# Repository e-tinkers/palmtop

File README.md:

# PalmTop - STM32G070-based Handheld

This repository contains the Kicad schematic and PCB files, plus hardware test sketch for 
[PalmTop](https://www.e-tinkers.com/2023/06/build-a-palmtop-handheld-with-stm32g070-part-1/) project.

![PalmTop - STM32G070-based 
handheld](https://www.e-tinkers.com/wp-content/uploads/2023/06/PalmTop_STM32G070.png)

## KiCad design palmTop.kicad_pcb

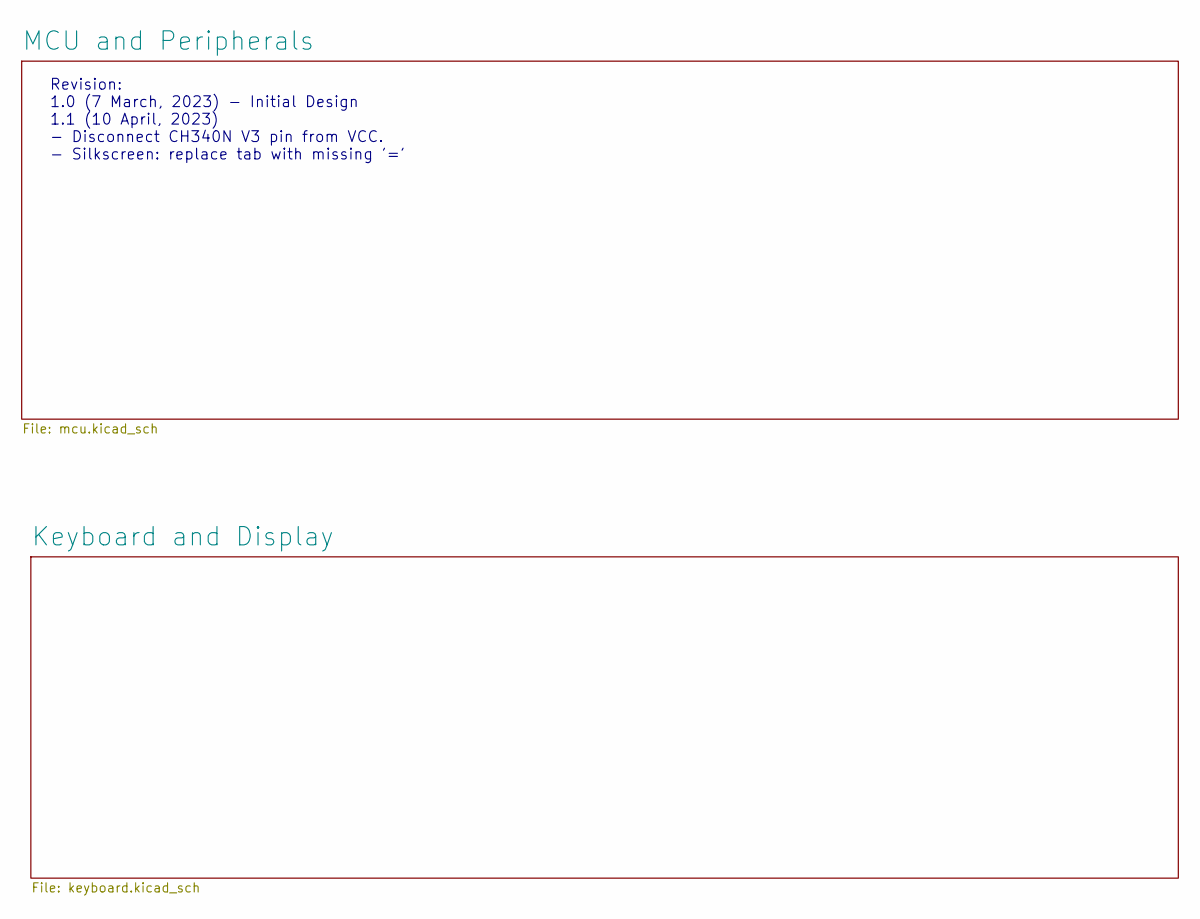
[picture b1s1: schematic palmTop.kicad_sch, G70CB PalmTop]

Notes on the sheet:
Revision: 1.0 (7 March, 2023) - Initial Design 1.1 (10 April, 2023) - Disconnect CH340N V3 pin from VCC. - Silkscreen: replace tab with missing '='

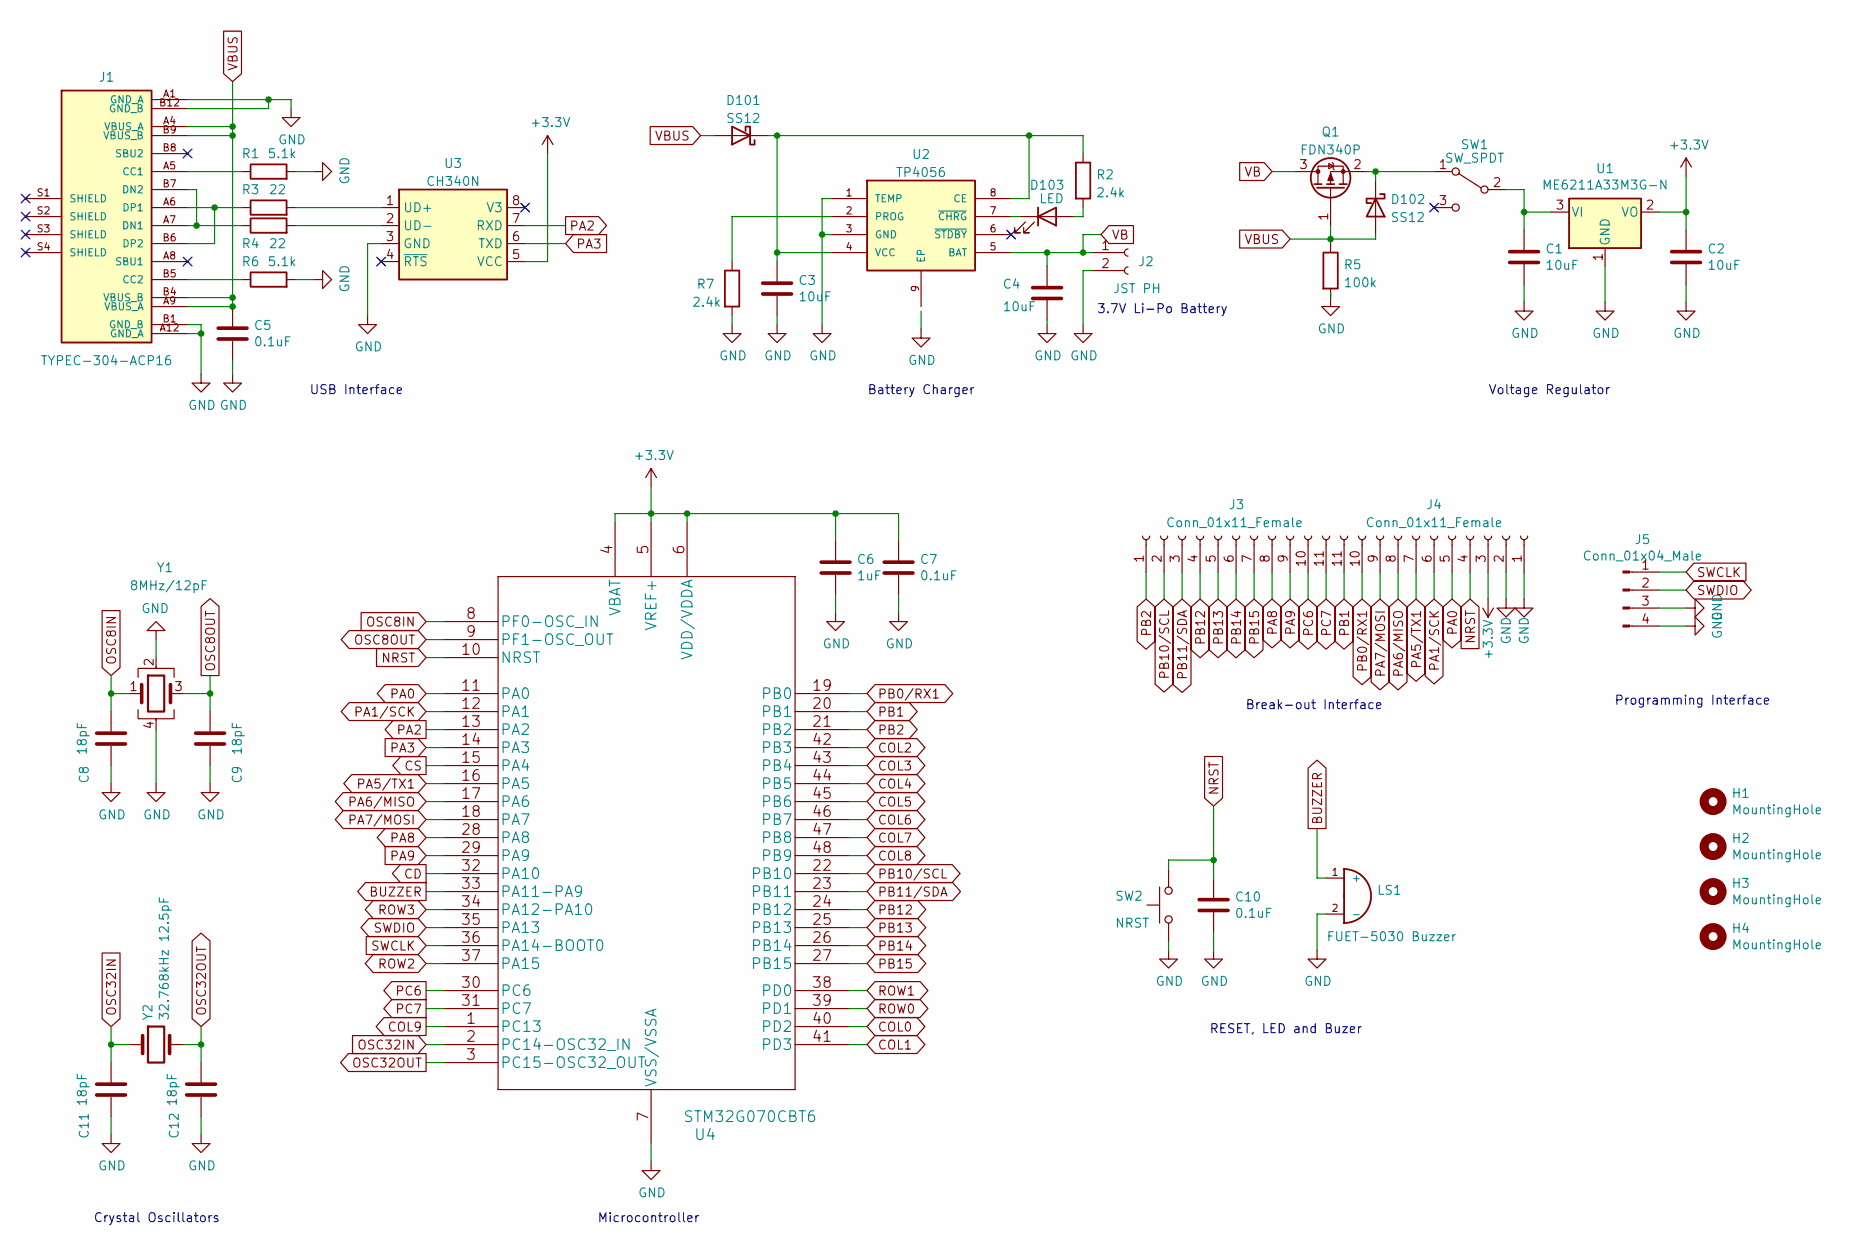
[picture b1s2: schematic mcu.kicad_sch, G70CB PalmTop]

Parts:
C1, C2, C3, C4: 10uF; C_0603_1608Metric_Pad1.08x0.95mm_HandSolder
C5, C7, C10: 0.1uF; C_0603_1608Metric_Pad1.08x0.95mm_HandSolder
C6: 1uF; C_0603_1608Metric_Pad1.08x0.95mm_HandSolder
C8, C9, C11, C12: 18pF; C_0603_1608Metric_Pad1.08x0.95mm_HandSolder
D101, D102: SS12; D_SMA
D103: LED; LED_0603_1608Metric_Pad1.05x0.95mm_HandSolder
H1, H2, H3, H4: MountingHole; MountingHole_3.2mm_M3
J1: TYPEC-304-ACP16; XUNPU_TYPEC-304-ACP16
J2: JST PH; JST_PH_S2B-PH-K_1x02_P2.00mm_Horizontal
J3, J4: Conn_01x11_Female; PinSocket_1x11_P2.54mm_Horizontal
J5: Conn_01x04_Male; PinHeader_1x04_P2.54mm_Horizontal
LS1: FUET-5030 Buzzer; FUET-5030-BUZZER
Q1: FDN340P; SOT-23
R1, R6: 5.1k; R_0603_1608Metric_Pad0.98x0.95mm_HandSolder
R2, R7: 2.4k; R_0603_1608Metric_Pad0.98x0.95mm_HandSolder
R3, R4: 22; R_0603_1608Metric_Pad0.98x0.95mm_HandSolder
R5: 100k; R_0603_1608Metric_Pad0.98x0.95mm_HandSolder
SW1: SW_SPDT; SW_SPDT_XKB_SK-3390A-L1
SW2: NRST; SW_TS-1185-X-X
U1: ME6211A33M3G-N; SOT-23
U2: TP4056; SOP127P600X175-9N
U3: CH340N; SOP-8_3.76x4.96mm_P1.27mm
U4: STM32G070CBT6; LQFP-48_7x7mm_P0.5mm
Y1: 8MHz/12pF; Crystal_SMD_3225-4Pin_3.2x2.5mm
Y2: 32.768kHz 12.5pF; Crystal_SMD_3215-2Pin_3.2x1.5mm

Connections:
BUZZER: LS1.1 (+), U4.33 (PA11-PA9)
+3V3: C2.1, C6.1, C7.1, J4.3, U1.2 (VO), U3.5 (VCC), U4.4 (VBAT), U4.5 (VREF+), U4.6 (VDD/VDDA); also elsewhere on the board
CD: U4.32 (PA10); also elsewhere on the board
COL0: U4.40 (PD2); also elsewhere on the board
COL1: U4.41 (PD3); also elsewhere on the board
COL2: U4.42 (PB3); also elsewhere on the board
COL3: U4.43 (PB4); also elsewhere on the board
COL4: U4.44 (PB5); also elsewhere on the board
COL5: U4.45 (PB6); also elsewhere on the board
COL6: U4.46 (PB7); also elsewhere on the board
COL7: U4.47 (PB8); also elsewhere on the board
COL8: U4.48 (PB9); also elsewhere on the board
COL9: U4.1 (PC13); also elsewhere on the board
CS: U4.15 (PA4); also elsewhere on the board
GND: C1.2, C2.2, C3.2, C4.2, C5.2, C6.2, C7.2, C8.2, C9.2, C10.1, C11.2, C12.2, J1.A1 (GND_A), J1.A12 (GND_A), J1.B1 (GND_B), J1.B12 (GND_B), J2.2, J4.1, J4.2, J5.3, J5.4, LS1.2 (-), R1.2, R5.2, R6.2, R7.2, SW2.1, U1.1 (GND), U2.1 (TEMP), U2.3 (GND), U3.3 (GND), U4.7 (VSS/VSSA), Y1.2, Y1.4; also elsewhere on the board
NRST: C10.2, J4.4, SW2.2, U4.10 (NRST); also elsewhere on the board
unnamed: C1.1, SW1.2 (B), U1.3 (VI)
unnamed: C3.1, D101.1 (K), R2.1, U2.4 (VCC), U2.8 (CE)
unnamed: D102.1 (K), Q1.2 (S), SW1.1 (A)
unnamed: D103.1 (K), U2.7 (~CHRG)
unnamed: D103.2 (A), R2.2
unnamed: J1.A5 (CC1), R1.1
unnamed: J1.A6 (DP1), J1.B6 (DP2), R3.1
unnamed: J1.A7 (DN1), J1.B7 (DN2), R4.1
unnamed: J1.B5 (CC2), R6.1
unnamed: R3.2, U3.1 (UD+)
unnamed: R4.2, U3.2 (UD-)
unnamed: R7.1, U2.2 (PROG)
OSC8IN: C8.1, U4.8 (PF0-OSC_IN), Y1.1
OSC8OUT: C9.1, U4.9 (PF1-OSC_OUT), Y1.3
OSC32IN: C11.1, U4.2 (PC14-OSC32_IN), Y2.1
OSC32OUT: C12.1, U4.3 (PC15-OSC32_OUT), Y2.2
PA0: J4.5, U4.11 (PA0)
PA1/SCK: J4.6, U4.12 (PA1); also elsewhere on the board
PA2: U3.7 (RXD), U4.13 (PA2)
PA3: U3.6 (TXD), U4.14 (PA3)
PA5/TX1: J4.7, U4.16 (PA5)
PA6/MISO: J4.8, U4.17 (PA6)
PA7/MOSI: J4.9, U4.18 (PA7); also elsewhere on the board
PA8: J3.8, U4.28 (PA8)
PA9: J3.9, U4.29 (PA9)
PB0/RX1: J4.10, U4.19 (PB0)
PB1: J4.11, U4.20 (PB1)
PB2: J3.1, U4.21 (PB2)
PB10/SCL: J3.2, U4.22 (PB10)
PB11/SDA: J3.3, U4.23 (PB11)
PB12: J3.4, U4.24 (PB12)
PB13: J3.5, U4.25 (PB13)
PB14: J3.6, U4.26 (PB14)
PB15: J3.7, U4.27 (PB15)
PC6: J3.10, U4.30 (PC6)
PC7: J3.11, U4.31 (PC7)
ROW0: U4.39 (PD1); also elsewhere on the board
ROW1: U4.38 (PD0); also elsewhere on the board
ROW2: U4.37 (PA15); also elsewhere on the board
ROW3: U4.34 (PA12-PA10); also elsewhere on the board
SWCLK: J5.1, U4.36 (PA14-BOOT0)
SWDIO: J5.2, U4.35 (PA13)
VB: C4.1, J2.1, Q1.3 (D), U2.5 (BAT)
VBUS: C5.1, D101.2 (A), D102.2 (A), J1.A4 (VBUS_A), J1.A9 (VBUS_A), J1.B4 (VBUS_B), J1.B9 (VBUS_B), Q1.1 (G), R5.1

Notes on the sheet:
RESET, LED and Buzer
Battery Charger
Microcontroller
USB Interface
Voltage Regulator
3.7V Li-Po Battery
Crystal Oscillators
Programming Interface
Break-out Interface

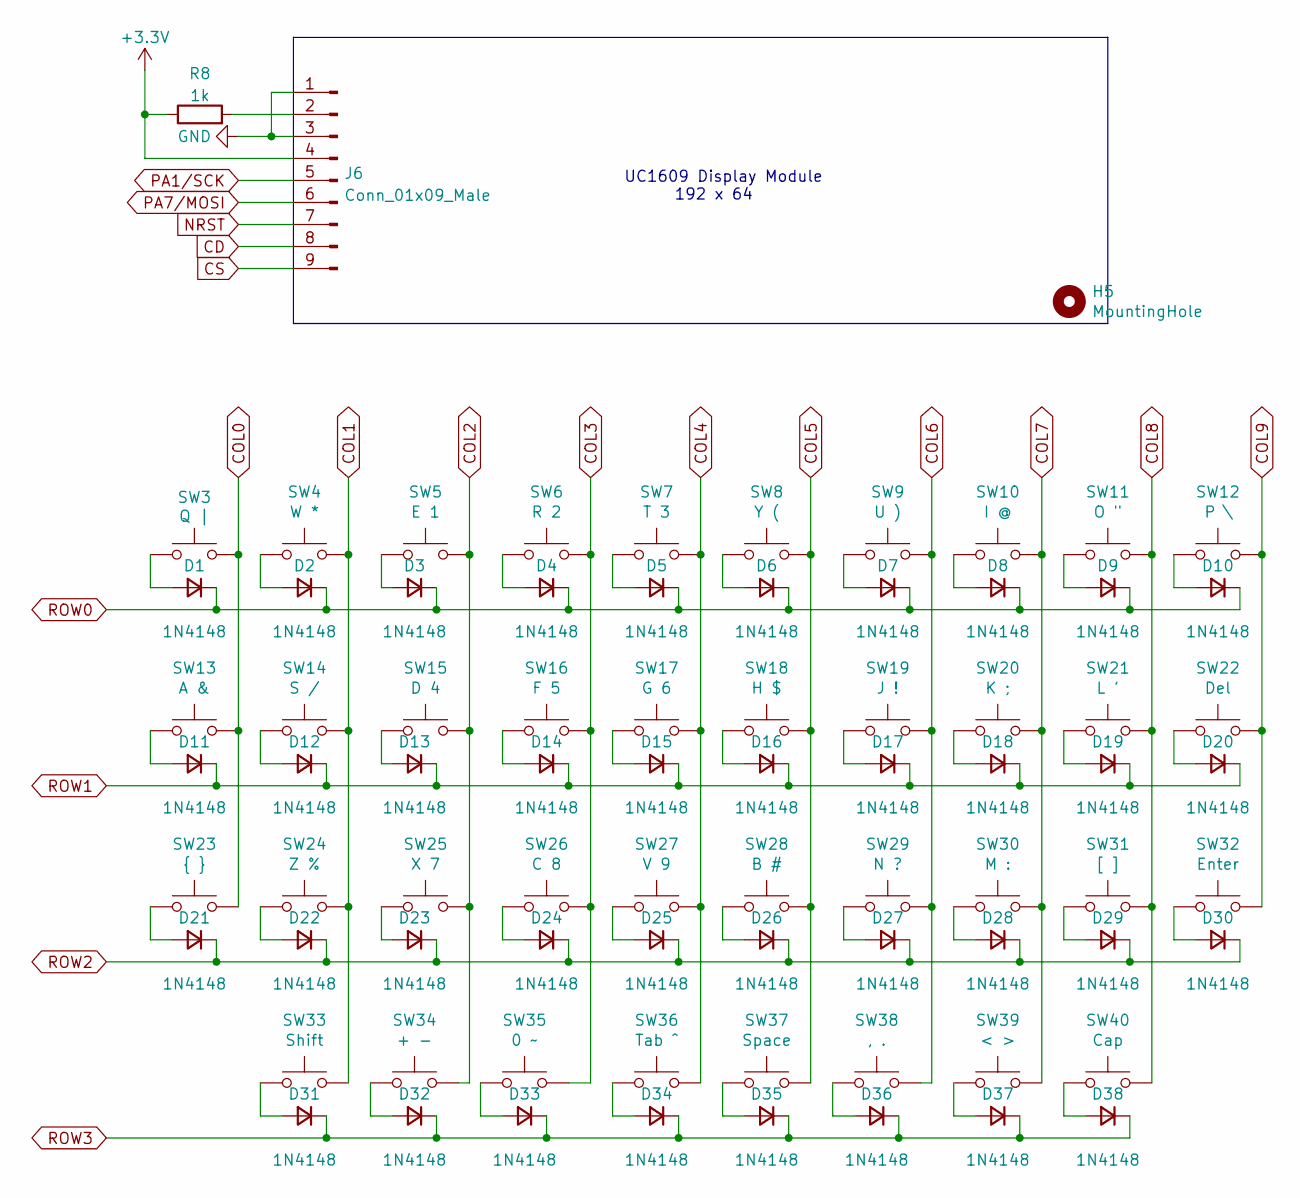
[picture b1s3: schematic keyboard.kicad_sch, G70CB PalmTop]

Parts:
D1, D2, D3, D4, D5, D6, D7, D8, D9, D10, D11, D12, D13, D14, D15, D16, D17, D18, D19, D20, D21, D22, D23, D24, D25, D26, D27, D28, D29, D30, D31, D32, D33, D34, D35, D36, D37, D38: 1N4148; D_SOD-123
H5: MountingHole; MountingHole_2.7mm_M2.5
J6: Conn_01x09_Male; PinHeader_1x09_P2.54mm_Vertical
R8: 1k; R_0603_1608Metric_Pad0.98x0.95mm_HandSolder
SW3: Q |; SW_PUSH_6mm_XKB_TC-1102-X-X-X
SW4: W *; SW_PUSH_6mm_XKB_TC-1102-X-X-X
SW5: E 1; SW_PUSH_6mm_XKB_TC-1102-X-X-X
SW6: R 2; SW_PUSH_6mm_XKB_TC-1102-X-X-X
SW7: T 3; SW_PUSH_6mm_XKB_TC-1102-X-X-X
SW8: Y (; SW_PUSH_6mm_XKB_TC-1102-X-X-X
SW9: U ); SW_PUSH_6mm_XKB_TC-1102-X-X-X
SW10: I @; SW_PUSH_6mm_XKB_TC-1102-X-X-X
SW11: O "; SW_PUSH_6mm_XKB_TC-1102-X-X-X
SW12: P \; SW_PUSH_6mm_XKB_TC-1102-X-X-X
SW13: A &; SW_PUSH_6mm_XKB_TC-1102-X-X-X
SW14: S /; SW_PUSH_6mm_XKB_TC-1102-X-X-X
SW15: D 4; SW_PUSH_6mm_XKB_TC-1102-X-X-X
SW16: F 5; SW_PUSH_6mm_XKB_TC-1102-X-X-X
SW17: G 6; SW_PUSH_6mm_XKB_TC-1102-X-X-X
SW18: H $; SW_PUSH_6mm_XKB_TC-1102-X-X-X
SW19: J !; SW_PUSH_6mm_XKB_TC-1102-X-X-X
SW20: K ;; SW_PUSH_6mm_XKB_TC-1102-X-X-X
SW21: L '; SW_PUSH_6mm_XKB_TC-1102-X-X-X
SW22: Del; SW_PUSH_6mm_XKB_TC-1102-X-X-X
SW23: { }; SW_PUSH_6mm_XKB_TC-1102-X-X-X
SW24: Z %; SW_PUSH_6mm_XKB_TC-1102-X-X-X
SW25: X 7; SW_PUSH_6mm_XKB_TC-1102-X-X-X
SW26: C 8; SW_PUSH_6mm_XKB_TC-1102-X-X-X
SW27: V 9; SW_PUSH_6mm_XKB_TC-1102-X-X-X
SW28: B #; SW_PUSH_6mm_XKB_TC-1102-X-X-X
SW29: N ?; SW_PUSH_6mm_XKB_TC-1102-X-X-X
SW30: M :; SW_PUSH_6mm_XKB_TC-1102-X-X-X
SW31: [ ]; SW_PUSH_6mm_XKB_TC-1102-X-X-X
SW32: Enter; SW_PUSH_6mm_XKB_TC-1102-X-X-X
SW33: Shift; SW_PUSH_6mm_XKB_TC-1102-X-X-X
SW34: + -; SW_PUSH_6mm_XKB_TC-1102-X-X-X
SW35: 0 ~; SW_PUSH_6mm_XKB_TC-1102-X-X-X
SW36: Tab ^; SW_PUSH_6mm_XKB_TC-1102-X-X-X
SW37: Space; SW_PUSH_6mm_XKB_TC-1102-X-X-X
SW38: , .; SW_PUSH_6mm_XKB_TC-1102-X-X-X
SW39: < >; SW_PUSH_6mm_XKB_TC-1102-X-X-X
SW40: Cap; SW_PUSH_6mm_XKB_TC-1102-X-X-X

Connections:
+3V3: J6.4, R8.1; also elsewhere on the board
CD: J6.8; also elsewhere on the board
COL0: SW3.2, SW13.2, SW23.2; also elsewhere on the board
COL1: SW4.2, SW14.2, SW24.2, SW33.2; also elsewhere on the board
COL2: SW5.2, SW15.2, SW25.2, SW34.2; also elsewhere on the board
COL3: SW6.2, SW16.2, SW26.2, SW35.2; also elsewhere on the board
COL4: SW7.2, SW17.2, SW27.2, SW36.2; also elsewhere on the board
COL5: SW8.2, SW18.2, SW28.2, SW37.2; also elsewhere on the board
COL6: SW9.2, SW19.2, SW29.2, SW38.2; also elsewhere on the board
COL7: SW10.2, SW20.2, SW30.2, SW39.2; also elsewhere on the board
COL8: SW11.2, SW21.2, SW31.2, SW40.2; also elsewhere on the board
COL9: SW12.2, SW22.2, SW32.2; also elsewhere on the board
CS: J6.9; also elsewhere on the board
GND: J6.1, J6.3; also elsewhere on the board
NRST: J6.7; also elsewhere on the board
unnamed: D1.2 (A), SW3.1
unnamed: D2.2 (A), SW4.1
unnamed: D3.2 (A), SW5.1
unnamed: D4.2 (A), SW6.1
unnamed: D5.2 (A), SW7.1
unnamed: D6.2 (A), SW8.1
unnamed: D7.2 (A), SW9.1
unnamed: D8.2 (A), SW10.1
unnamed: D9.2 (A), SW11.1
unnamed: D10.2 (A), SW12.1
unnamed: D11.2 (A), SW13.1
unnamed: D12.2 (A), SW14.1
unnamed: D13.2 (A), SW15.1
unnamed: D14.2 (A), SW16.1
unnamed: D15.2 (A), SW17.1
unnamed: D16.2 (A), SW18.1
unnamed: D17.2 (A), SW19.1
unnamed: D18.2 (A), SW20.1
unnamed: D19.2 (A), SW21.1
unnamed: D20.2 (A), SW22.1
unnamed: D21.2 (A), SW23.1
unnamed: D22.2 (A), SW24.1
unnamed: D23.2 (A), SW25.1
unnamed: D24.2 (A), SW26.1
unnamed: D25.2 (A), SW27.1
unnamed: D26.2 (A), SW28.1
unnamed: D27.2 (A), SW29.1
unnamed: D28.2 (A), SW30.1
unnamed: D29.2 (A), SW31.1
unnamed: D30.2 (A), SW32.1
unnamed: D31.2 (A), SW33.1
unnamed: D32.2 (A), SW34.1
unnamed: D33.2 (A), SW35.1
unnamed: D34.2 (A), SW36.1
unnamed: D35.2 (A), SW37.1
unnamed: D36.2 (A), SW38.1
unnamed: D37.2 (A), SW39.1
unnamed: D38.2 (A), SW40.1
unnamed: J6.2, R8.2
PA1/SCK: J6.5; also elsewhere on the board
PA7/MOSI: J6.6; also elsewhere on the board
ROW0: D1.1 (K), D2.1 (K), D3.1 (K), D4.1 (K), D5.1 (K), D6.1 (K), D7.1 (K), D8.1 (K), D9.1 (K), D10.1 (K); also elsewhere on the board
ROW1: D11.1 (K), D12.1 (K), D13.1 (K), D14.1 (K), D15.1 (K), D16.1 (K), D17.1 (K), D18.1 (K), D19.1 (K), D20.1 (K); also elsewhere on the board
ROW2: D21.1 (K), D22.1 (K), D23.1 (K), D24.1 (K), D25.1 (K), D26.1 (K), D27.1 (K), D28.1 (K), D29.1 (K), D30.1 (K); also elsewhere on the board
ROW3: D31.1 (K), D32.1 (K), D33.1 (K), D34.1 (K), D35.1 (K), D36.1 (K), D37.1 (K), D38.1 (K); also elsewhere on the board

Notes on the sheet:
UC1609 Display Module 192 x 64

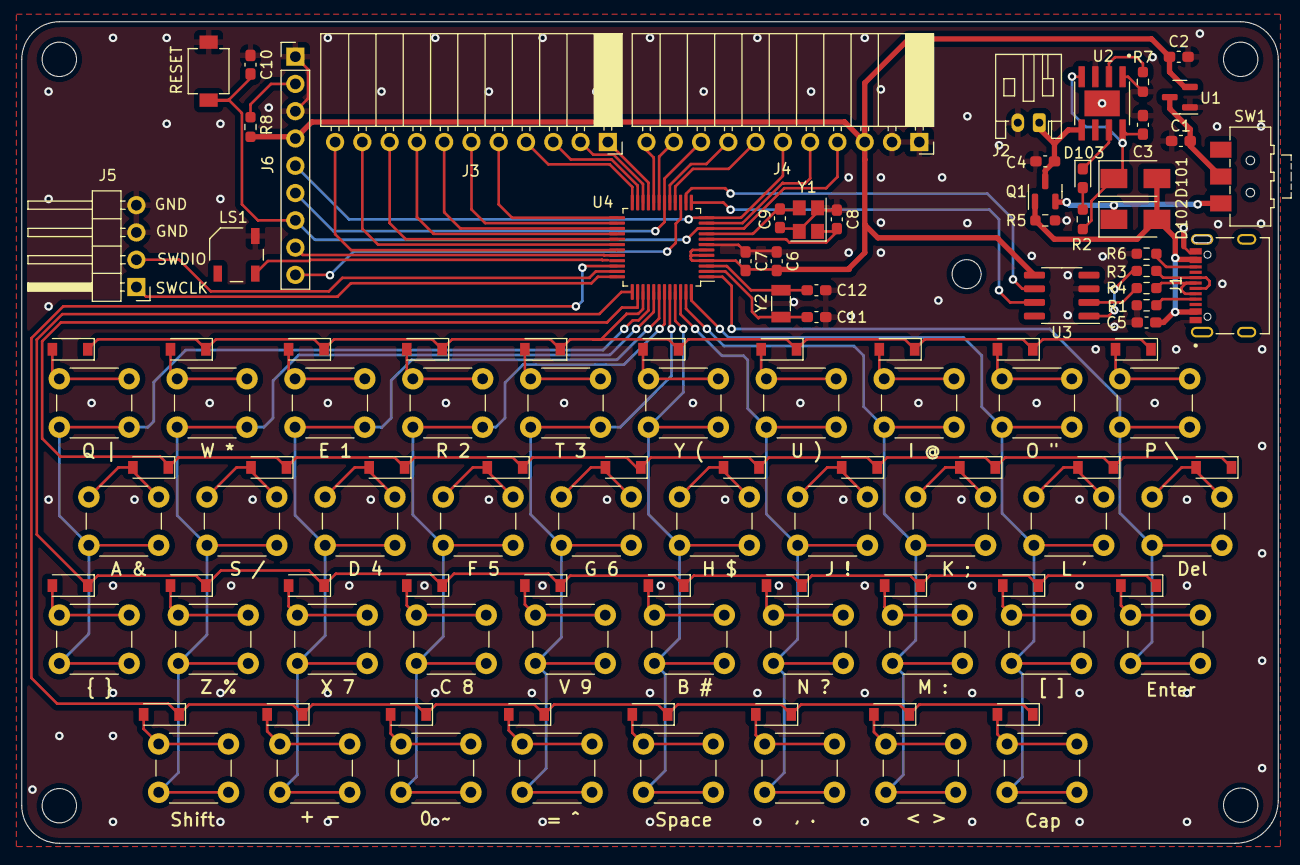
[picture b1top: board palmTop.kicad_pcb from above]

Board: 2 copper layers, 117.0 x 76.5 mm, 120 parts (0 on the bottom side), 99 nets.

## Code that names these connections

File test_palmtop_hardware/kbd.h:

#ifndef _KBD_H_
#define _KBD_H_
/*
 *  The Keyboard is a full function keyboard inspired by Palm Treo650 keyboard.
 *  The keyboard matrix code is based on the original work by Mark Stanley and Alexander Brevig
 *  from http://playground.arduino.cc/Code/Keypad.
 *  
 */
#include <Arduino.h>

#define NAK  0x0   // Not a key
#define SO   0xE   // For representing CapLock key
#define SI   0xF   // For representing Shift key

#define ROWS 4
#define COLS 10

#define BUZZER   PA11

enum {NORMAL, SHIFTED, CAPLOCK};

#define DEBOUNCED_INTERVAL 150

class Keyboard
{
public:

  void begin(void);
  char available();
  char read();

private:

  // GPIO Pins for keyboard matrix
  const uint8_t rowPins[ROWS] = {PD1, PD0, PA15, PA12};  // Row0 - Row3
  const uint8_t colPins[COLS] = {PD2, PD3, PB3, PB4, PB5, PB6, PB7, PB8, PB9, PC13}; //Col0 - Col9

  // Keyboard character map
  const char keys[ROWS][COLS] = {
    // Without Shift
    {'q', 'w', 'e', 'r', 't', 'y', 'u', 'i', 'o', 'p'},
    {'a', 's', 'd', 'f', 'g', 'h', 'j', 'k', 'l', '\b'},
    {'{', 'z', 'x', 'c', 'v', 'b', 'n', 'm', '[', '\n'},
    {NAK,  SI, '+', '~', '=',' ', ',', '<', SO, NAK}
  };
  const char keysShifted[4][10] = {
    // With shift
    {'|', '*', '1', '2', '3', '(', ')', '@', '\"', '\\'},
    {'&', '/', '4', '5', '6', '$', '!', ';', '\'', '\b'},
    {'}', '%', '7', '8', '9', '#', '?', ':', ']', '\n'},
    {NAK, SI, '-', '0', '^', ' ', '.', '>', SO, NAK}
  };

  uint8_t _keyState{NORMAL};
  char _keyCode{0};
};

#endif

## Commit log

2023-06-25 add README
2023-06-25 update image link
2023-06-25 update silkscreen to replace 'tab' with '='

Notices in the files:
palmTop.kicad_pcb:
Copyright 2023, e-tinkers.com
